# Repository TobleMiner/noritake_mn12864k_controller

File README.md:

Noritake MN12864K VFD controller
================================

The Noritake MN12864K is a 128x64 pixel dot-matrix vacuum fluorescent
display.  
The hardware described in this repository is a controller board allowing
control of the VFD via SPI, I2C or USB and supply from a single 5V supply.

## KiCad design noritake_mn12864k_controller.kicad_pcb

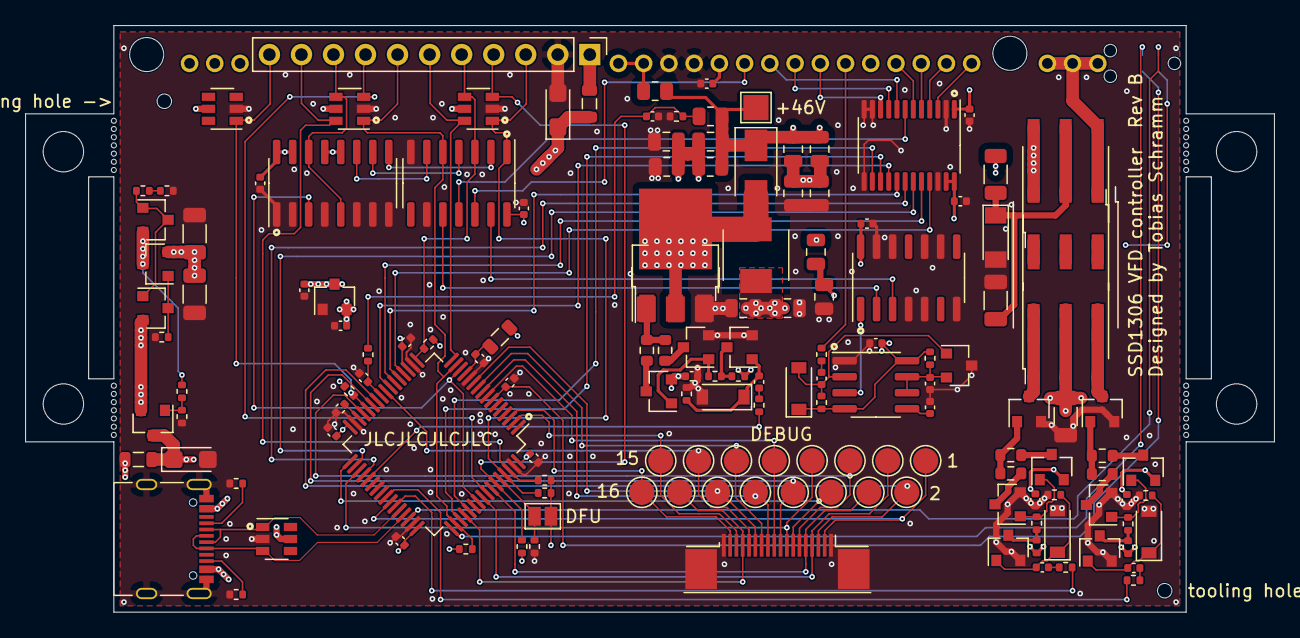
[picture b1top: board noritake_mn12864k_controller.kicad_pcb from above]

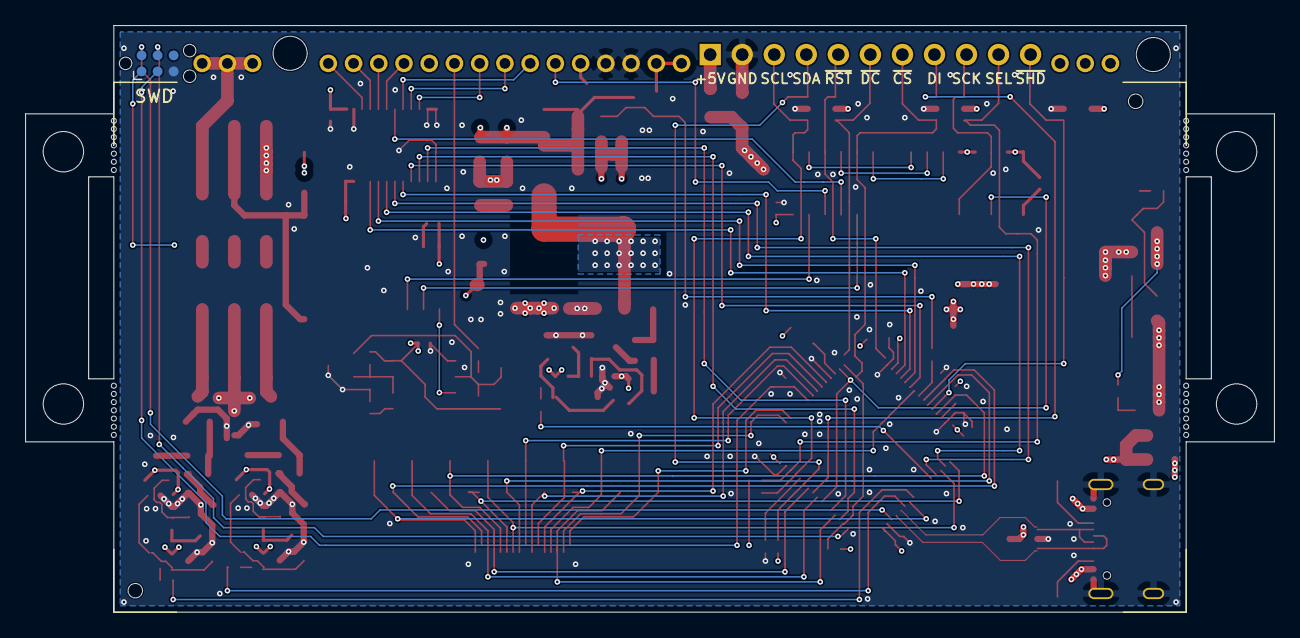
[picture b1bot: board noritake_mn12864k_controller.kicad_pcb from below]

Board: 4 copper layers, 99.0 x 46.5 mm, 187 parts (3 on the bottom side), 113 nets.

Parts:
C1, C10: 10uF; CP_EIA-3216-12_Kemet-S
C2, C3, C5, C6, C9, C11, C15, C16, C19, C20, C22, C23, C24, C25, C26, C27, C31, C32, C34, C36: 100nF; C_0402_1005Metric
C4, C18, C21, C33, C37: 1uF; C_0402_1005Metric
C7: 10uF; C_1206_3216Metric
C8: 4.7uF; C_1206_3216Metric
C12: 1nF; C_0402_1005Metric
C13, C14: 47uF; C_1206_3216Metric
C17: 4.7uF; C_0402_1005Metric
C28, C29: 10uF LV; C_0805_2012Metric
C30, C35, C38, C39, C40, C41, C42, C43: 10uF; C_0805_2012Metric
D1: 5V6; D_MiniMELF
D2: SS210; D_SMA
D3, D4, D5, D7: B5819W; D_SOD-123
FB1, FB2, FB3: Ferrite_Bead; L_0805_2012Metric
H1, H2: ToolingHole; ToolingHole_JLCSMT
H3, H4: MountingHole; MountingHole_2.7mm_M2.5
H5, H6, H7, H8: MountingHole; MountingHole_3.2mm_M3
H9, H10, H11, H12, H13, H14, H15, H16, H17, H18, H19, H20, H21, H22, H23, H24, H25, H26, H27, H28, H29, H30, H31, H32, H33, H34, H35, H36: Perforation; Perforation_0.4mm
J1: Conn_01x11; PinHeader_1x11_P2.54mm_Vertical
J2: USB_C_Receptacle_USB2.0; USB_C_Receptacle_Palconn_UTC16-G
J3: TagConnect_TC2030_SWD; Tag-Connect_TC2030-IDC-NL_2x03_P1.27mm_Vertical
J4: Conn_01x18; MINTRON-LW05202-18
JP1: DFU; SolderJumper-2_P1.3mm_Open_Pad1.0x1.5mm
L1: 22uH; MWSA0503S
Q1, Q2: AO3400A; SOT-23
Q3, Q6, Q18: S9015; SOT-23
Q4, Q5: AO3401A; SOT-23
Q7, Q9, Q10, Q12, Q15, Q17: 2N7002; SOT-23
Q8, Q11, Q16: LBSS84LT1G; SOT-23
Q13: TO-252; TO-252-3_TabPin2
Q14: CJT04N15; SOT-223-3_TabPin2
R1, R15, R20, R34, R37, R39, R42: 50R; R_0402_1005Metric
R2, R11, R12, R14, R16, R23, R24, R25, R26, R27, R28, R35: 100kR; R_0402_1005Metric
R3, R4, R6, R29: 5.1kR; R_0402_1005Metric
R5: 10kR; R_1206_3216Metric
R7: 22R; R_0805_2012Metric
R8, R9: 33kR; R_0402_1005Metric
R10: 1kR; R_0402_1005Metric
R13: 1MR; R_0402_1005Metric
R17, R18, R21, R22, R40, R41: 33R; R_0603_1608Metric
R19, R36, R38: 470R; R_0402_1005Metric
R30, R31, R32: 100kR; R_0805_2012Metric
R33: 3.3kR; R_0402_1005Metric
T1, T2, T3: Wuerth 760390013; Transformer_Würth_10.05x6.73_6P
T4: Wuerth 760390013; Transformer_Würth_12.60x8.30_6P
TP1: DEBUG00; TestPoint_Pad_D2.0mm
TP2: DEBUG06; TestPoint_Pad_D2.0mm
TP3: DEBUG07; TestPoint_Pad_D2.0mm
TP4: DEBUG08; TestPoint_Pad_D2.0mm
TP5: DEBUG09; TestPoint_Pad_D2.0mm
TP6: DEBUG10; TestPoint_Pad_D2.0mm
TP7: DEBUG11; TestPoint_Pad_D2.0mm
TP8: DEBUG12; TestPoint_Pad_D2.0mm
TP9: DEBUG13; TestPoint_Pad_D2.0mm
TP10: DEBUG14; TestPoint_Pad_D2.0mm
TP11: DEBUG15; TestPoint_Pad_D2.0mm
TP12: DEBUG05; TestPoint_Pad_D2.0mm
TP13: DEBUG01; TestPoint_Pad_D2.0mm
TP14: DEBUG02; TestPoint_Pad_D2.0mm
TP15: DEBUG03; TestPoint_Pad_D2.0mm
TP16: DEBUG04; TestPoint_Pad_D2.0mm
TP17: +48V; TestPoint_Pad_2.0x2.0mm
U1: SN74AVC8T245PW; TSSOP-24_4.4x7.8mm_P0.65mm
U2: 74HC14; SOIC-14_3.9x8.7mm_P1.27mm
U3: CD4051B; SOIC-16_3.9x9.9mm_P1.27mm
U4: MN12864K
U5: STM32F730R8T6; LQFP-64_10x10mm_P0.5mm
U6: NE555D; SOIC-8_3.9x4.9mm_P1.27mm
U7: 74HC08; SOIC-14_3.9x8.7mm_P1.27mm
U8, U10, U11, U12: SRV05-4; SOT-23-6
U9: XC6206PxxxMR; SOT-23

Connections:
+3V3: C5.1, C19.2, C20.2, C21.1, C22.2, C23.2, FB3.2, J3.1, JP1.2, R23.1, R24.1, R25.1, R26.1, R27.1, R28.1, U1.23, U1.24, U5.19, U5.32, U5.48, U5.64, U9.2
+5V: C2.2, C4.2, C6.2, C7.1, C9.1, C11.2, C13.1, C14.1, C18.2, C25.2, C27.2, C28.2, C29.2, C33.2, C37.2, D7.1, L1.1, Q4.2, Q5.2, Q6.2, Q8.2, Q11.2, Q16.2, R13.1, R14.1, R19.1, R36.1, R38.1, T1.5, T2.2, T4.5, U1.1, U2.14, U3.12, U3.13, U3.15, U3.16, U4.16, U6.4, U6.8, U7.14, U9.3, U10.5, U11.5, U12.5
+48V: C35.1, C38.1, C40.1, C42.1, D2.1, R5.1, R7.1, R30.1, R32.1, TP17.1
/4WIRE: J1.4, R26.2, U5.59, U10.3
/CPOL: J1.3, R27.2, U2.1, U5.61, U10.1
/D+: J2.A6, J2.B6, U5.45, U8.3
/D-: J2.A7, J2.B7, U5.44, U8.1
/DBG00: J4.2, TP1.1, U5.42
/DBG01: J4.3, TP13.1, U5.26
/DBG02: J4.4, TP14.1, U5.56
/DBG03: J4.5, TP15.1, U5.58
/DBG04: J4.6, TP16.1, U5.29
/DBG05: J4.7, TP12.1, U5.33
/DBG06: J4.8, TP2.1, U5.35
/DBG07: J4.9, TP3.1, U5.27
/DBG08: J4.10, TP4.1, U5.8
/DBG09: J4.11, TP5.1, U5.9
/DBG10: J4.12, TP6.1, U5.10
/DBG11: J4.13, TP7.1, U5.11
/DBG12: J4.14, TP8.1, U5.24
/DBG13: J4.15, TP9.1, U5.52
/DBG14: J4.16, TP10.1, U5.2
/DBG15: J4.17, TP11.1, U5.3
/IFSEL: J1.10, R25.2, U5.62, U11.6
/MOSI: J1.8, U5.57, U11.3
/SCK: J1.9, U3.5, U3.14, U11.4
/SCK_GATED: U3.3, U5.14, U5.55
/SWCLK: J3.4, U5.49
/SWDIO: J3.2, U5.46
/VBUS_HDR: C1.1, FB1.1, Q3.2, Q4.3, R10.2
/VBUS_USB: C10.1, FB2.1, Q5.3, U8.5
/VCC: FB1.2, J1.1
/VFD/STEPUP_FB: C31.2, R29.2, R32.2, R33.1
/VFD/VFD_GSOUT: R42.2, U4.11
/VFD/sheet60B1BFBD/GBLK_IN: U1.7, U2.11
/VFD/sheet60B1BFBD/GBLK_OUT: U2.12, U4.15
/VFD/sheet60B1BFBE/OUT: Q1.1, R17.1, R18.1
/VFD/sheet60B1BFBF/OUT: Q2.1, R21.1, R22.1
/VFD/sheet6147410A/OUT: Q13.1, Q14.1, R40.1, R41.1
/VFD_BLK: U1.21, U5.20
/VFD_CLK: U1.19, U5.34
/VFD_GCLK: U1.15, U5.51
/VFD_GLAT: U1.16, U5.23
/VFD_GSBLK: U1.17, U5.21
/VFD_GSIN: U1.14, U5.53
/VFD_HTR_G1: R1.2, U5.41
/VFD_HTR_G2: R15.2, U5.43
/VFD_HV_FB: C34.2, R29.1, U5.25
/VFD_HV_G: R34.2, U5.37
/VFD_LAT: U1.20, U5.22
/VFD_SIN: U1.18, U5.36
/~CS: J1.7, R23.2, U2.5, U5.15, U5.50, U11.1
/~DC: J1.6, U5.16, U10.6
/~MCU_RST: C15.2, J3.3, U5.7
/~RST: J1.5, R24.2, U2.3, U5.17, U10.4
/~SHDWN: J1.11, R28.2, U5.28, U12.1
GND: C1.2, C2.1, C4.1, C5.2, C6.1, C7.2, C8.2, C9.2, C10.2, C11.1, C13.2, C14.2, C15.1, C16.1, C17.2, C18.1, C19.1, C20.1, C21.2, C22.1, C23.1, C24.2, C25.1, C26.2, C27.1, C28.1, C29.1, C30.2, C31.1, C33.1, C34.1, C37.1, C39.2, C41.2, C43.2, D1.2, D3.2, D4.2, D5.2, J1.2, J2.A1, J2.A12, J2.B1, J2.B12, J2.S1, J3.5, J4.1, J4.18, J4.MP, Q1.2, Q2.2, Q7.2, Q9.2, Q10.2, Q12.2, Q13.3, Q14.3, Q15.2, Q17.2, Q18.3, R2.2, R3.1, R4.2, R6.2, R9.2, R11.2, R12.2, R16.2, R31.2, R33.2, R35.2, U1.2, U1.11, U1.12, U1.13, U1.22, U2.7, U2.9, U3.1, U3.2, U3.4, U3.6, U3.7, U3.8, U4.17, U4.18, U5.12, U5.18, U5.31, U5.47, U5.63, U6.1, U7.4, U7.5, U7.7, U7.9, U7.10, U7.12, U7.13, U8.2, U9.1, U10.2, U11.2, U12.2
unnamed: C3.1, D3.1, Q7.1, R2.1
unnamed: C3.2, R1.1
unnamed: C8.1, D1.1, R5.2, T1.2, T3.5, T4.2
unnamed: C12.1, D7.2, Q18.1, R13.2, U6.2
unnamed: C12.2, R42.1
unnamed: C16.2, FB3.1, U5.13
unnamed: C17.1, U5.30
unnamed: C24.1, U6.5
unnamed: C26.1, Q18.2, R14.2, U6.6, U6.7
unnamed: C30.1, C35.2, C38.2, C39.1, C40.2, C41.1, C42.2, C43.1, R30.2, R31.1
unnamed: C32.1, D4.1, Q10.1, R16.1
unnamed: C32.2, R15.1
unnamed: C36.1, D5.1, Q15.1, R35.1
unnamed: C36.2, R34.1
unnamed: D2.2, L1.2, Q13.2, Q14.2
unnamed: FB2.2, J2.A4, J2.A9, J2.B4, J2.B9
unnamed: J2.A5, R3.2
unnamed: J2.B5, R4.1
unnamed: JP1.1, R6.1, U5.60
unnamed: Q1.3, T1.6, T2.3, T4.6
unnamed: Q2.3, T1.4, T2.1, T4.4
unnamed: Q3.1, Q3.3, Q6.1, R8.1
unnamed: Q4.1, Q6.3, R12.1
unnamed: Q5.1, R10.1, R11.1
unnamed: Q7.3, R19.2, R20.2
unnamed: Q8.1, Q9.1, R20.1
unnamed: Q8.3, R17.2
unnamed: Q9.3, R18.2
unnamed: Q10.3, R36.2, R37.2
unnamed: Q11.1, Q12.1, R37.1
unnamed: Q11.3, R21.2
unnamed: Q12.3, R22.2
unnamed: Q15.3, R38.2, R39.2
unnamed: Q16.1, Q17.1, R39.1
unnamed: Q16.3, R40.2
unnamed: Q17.3, R41.2
unnamed: R8.2, R9.1
unnamed: T1.1, T3.4, T4.1, U4.1, U4.2, U4.3
unnamed: T1.3, T3.6, T4.3, U4.35, U4.36, U4.37
unnamed: T2.4, T3.3
unnamed: T2.5, T3.2
unnamed: T2.6, T3.1
unnamed: U1.3, U4.6
unnamed: U1.4, U4.7
unnamed: U1.5, U4.8
unnamed: U1.6, U4.9
unnamed: U1.8, U4.14
unnamed: U1.9, U4.13
unnamed: U1.10, U4.12
unnamed: U2.2, U3.9
unnamed: U2.4, U3.10
unnamed: U2.6, U3.11
unnamed: U2.10, U7.2
unnamed: U2.13, U7.3
unnamed: U6.3, U7.1
VDD2: R7.2, U4.19, U4.20

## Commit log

2020-11-14 Connect shutdown and ifsel
2020-11-14 Add dual filament transformer option
2020-11-14 Add PA4/PA5 5V todo
2020-11-18 Add VFD section
2020-11-19 Fix grid protection
    Ensure only edges are detected
2020-11-20 Complete intra section layout
2020-11-20 Layout all nets
2020-11-20 Fix FFC courtyard
2020-11-21 Add some via stitching
2020-11-21 Add silkscreen markings
2020-11-21 Add more silkscreen markings
2020-11-21 Add pin 1 indicators
2020-11-21 Add missing LCSC partnumbers
2020-11-21 Add pin labels
2020-12-05 Fix level shifter
    Level shifter was flipped in scheatic
    Pressed "y" one too many times on that thing :/
2020-12-07 Equalize track spacing on debug connector
2020-12-07 Add additional VFD VDD2 bulk capacitance
2020-12-07 Add additional GND via
2020-12-07 Add more VFD VDD2 bulk capacitance
2020-12-07 Add optional mounting bracket
2020-12-07 Less diseased power routing
2020-12-07 Add more VFD VDD2 bypassing
2020-12-07 Fix accidentially disconnected caps
2020-12-07 Assign unique value to low voltage 0805 caps
2020-12-15 Add i2c address select pin
2023-03-18 Add basic readme
